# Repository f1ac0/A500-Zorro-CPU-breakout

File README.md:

# A500-Zorro-CPU-breakout
This is a breakout PCB with a DIP64 68000 CPU socket that plugs into the Amiga 500 expansion port. It has no active part and is designed to just move the original 68000 outside the system, host a 68000 CPU replacement, or an expansion designed to seat under the CPU. It should be helpful for design and test purposes, and may use a ZIF-64 socket.

It is designed as a 2 layers board and to fit in the dimensions for cheap PCB manufacturing ; because of this it requires an additional small board for the power pins of the expansion connector (or two additional wires).

Beware that the 68000 is rotated 180° from how it is on the A500 motherboard : its pin 1 is on the top left instead of bottom right. This made the PCB routing a bit more complicated but should allow to install the boards that normally expand over the ROM or Denise chips.

If your CPU replacement does not use bus arbitration to take over the 68k bus, then the CPU on the A500 motherboard must be removed.

Depending on your A500 motherboard revision, you may have to close its JP6 jumper to feed the 7MHz clock to the expansion connector.

# Disclaimer
This is a hobbyist project, it comes with no warranty and no support. Also remember that the Amiga machines are about 30 years old and may fail because of such hardware expansions.

I publish my work under the CC-BY-NC-SA license.

If you find it useful and want to reward my hard work : I am always looking for Amiga/Amstrad CPC/Commodore hardware to repair and hack, please contact me.

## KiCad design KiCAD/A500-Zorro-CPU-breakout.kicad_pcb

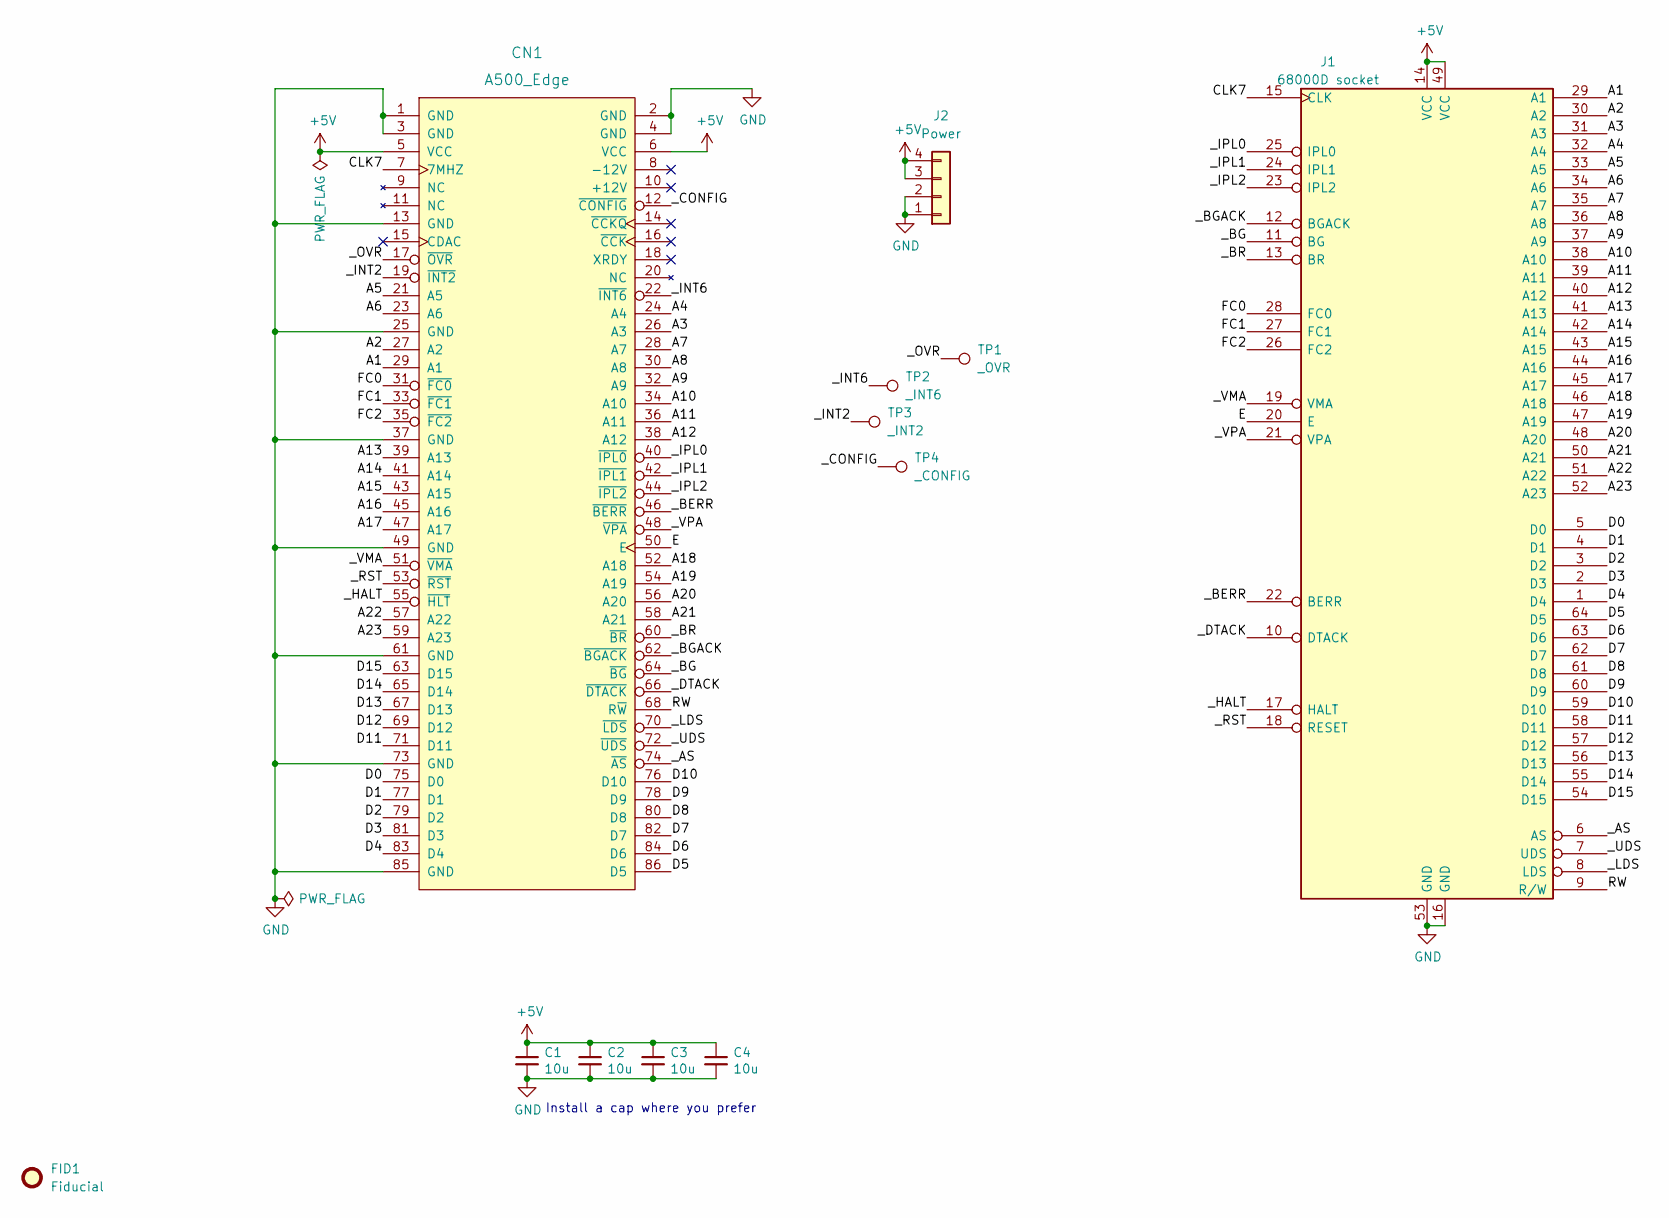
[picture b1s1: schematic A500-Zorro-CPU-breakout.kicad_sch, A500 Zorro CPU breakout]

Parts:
C1, C2, C3, C4: 10u; C_0805_2012Metric
CN1: A500_Edge; A500_ExpansionSocket_2x43_P2.54mm_5mm
FID1: Fiducial; CC_BY_NC_SA_long_silkscreen
J1: 68000D socket; DIP-64_W22.86mm_Socket_LongPads_BigHoles1.0
J2: Power; PinHeader_1x04_P2.54mm_Vertical
TP1: _OVR; TestPoint_THTPad_D1.7mm_Drill1.0mm
TP2: _INT6; TestPoint_THTPad_D1.7mm_Drill1.0mm
TP3: _INT2; TestPoint_THTPad_D1.7mm_Drill1.0mm
TP4: _CONFIG; TestPoint_THTPad_D1.7mm_Drill1.0mm

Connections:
+5V: C1.1, C2.1, C3.1, C4.1, CN1.5 (VCC), CN1.6 (VCC), J1.14 (VCC), J1.49 (VCC), J2.3, J2.4
/A1: CN1.29 (A1), J1.29 (A1)
/A2: CN1.27 (A2), J1.30 (A2)
/A3: CN1.26 (A3), J1.31 (A3)
/A4: CN1.24 (A4), J1.32 (A4)
/A5: CN1.21 (A5), J1.33 (A5)
/A6: CN1.23 (A6), J1.34 (A6)
/A7: CN1.28 (A7), J1.35 (A7)
/A8: CN1.30 (A8), J1.36 (A8)
/A9: CN1.32 (A9), J1.37 (A9)
/A10: CN1.34 (A10), J1.38 (A10)
/A11: CN1.36 (A11), J1.39 (A11)
/A12: CN1.38 (A12), J1.40 (A12)
/A13: CN1.39 (A13), J1.41 (A13)
/A14: CN1.41 (A14), J1.42 (A14)
/A15: CN1.43 (A15), J1.43 (A15)
/A16: CN1.45 (A16), J1.44 (A16)
/A17: CN1.47 (A17), J1.45 (A17)
/A18: CN1.52 (A18), J1.46 (A18)
/A19: CN1.54 (A19), J1.47 (A19)
/A20: CN1.56 (A20), J1.48 (A20)
/A21: CN1.58 (A21), J1.50 (A21)
/A22: CN1.57 (A22), J1.51 (A22)
/A23: CN1.59 (A23), J1.52 (A23)
/CLK7: CN1.7 (7MHZ), J1.15 (CLK)
/D0: CN1.75 (D0), J1.5 (D0)
/D1: CN1.77 (D1), J1.4 (D1)
/D2: CN1.79 (D2), J1.3 (D2)
/D3: CN1.81 (D3), J1.2 (D3)
/D4: CN1.83 (D4), J1.1 (D4)
/D5: CN1.86 (D5), J1.64 (D5)
/D6: CN1.84 (D6), J1.63 (D6)
/D7: CN1.82 (D7), J1.62 (D7)
/D8: CN1.80 (D8), J1.61 (D8)
/D9: CN1.78 (D9), J1.60 (D9)
/D10: CN1.76 (D10), J1.59 (D10)
/D11: CN1.71 (D11), J1.58 (D11)
/D12: CN1.69 (D12), J1.57 (D12)
/D13: CN1.67 (D13), J1.56 (D13)
/D14: CN1.65 (D14), J1.55 (D14)
/D15: CN1.63 (D15), J1.54 (D15)
/E: CN1.50 (E), J1.20 (E)
/FC0: CN1.31 (~FC0), J1.28 (FC0)
/FC1: CN1.33 (~FC1), J1.27 (FC1)
/FC2: CN1.35 (~FC2), J1.26 (FC2)
/RW: CN1.68 (R~W), J1.9 (R/W)
/_AS: CN1.74 (~AS), J1.6 (AS)
/_BERR: CN1.46 (~BERR), J1.22 (BERR)
/_BG: CN1.64 (~BG), J1.11 (BG)
/_BGACK: CN1.62 (~BGACK), J1.12 (BGACK)
/_BR: CN1.60 (~BR), J1.13 (BR)
/_CONFIG: CN1.12 (~CONFIG), TP4.1
/_DTACK: CN1.66 (~DTACK), J1.10 (DTACK)
/_HALT: CN1.55 (~HLT), J1.17 (HALT)
/_INT2: CN1.19 (~INT2), TP3.1
/_INT6: CN1.22 (~INT6), TP2.1
/_IPL0: CN1.40 (~IPL0), J1.25 (IPL0)
/_IPL1: CN1.42 (~IPL1), J1.24 (IPL1)
/_IPL2: CN1.44 (~IPL2), J1.23 (IPL2)
/_LDS: CN1.70 (~LDS), J1.8 (LDS)
/_OVR: CN1.17 (~OVR), TP1.1
/_RST: CN1.53 (~RST), J1.18 (RESET)
/_UDS: CN1.72 (~UDS), J1.7 (UDS)
/_VMA: CN1.51 (~VMA), J1.19 (VMA)
/_VPA: CN1.48 (~VPA), J1.21 (VPA)
GND: C1.2, C2.2, C3.2, C4.2, CN1.1 (GND), CN1.2 (GND), CN1.3 (GND), CN1.4 (GND), CN1.13 (GND), CN1.25 (GND), CN1.37 (GND), CN1.49 (GND), CN1.61 (GND), CN1.73 (GND), CN1.85 (GND), J1.16 (GND), J1.53 (GND), J2.1, J2.2

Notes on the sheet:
Install a cap where you prefer

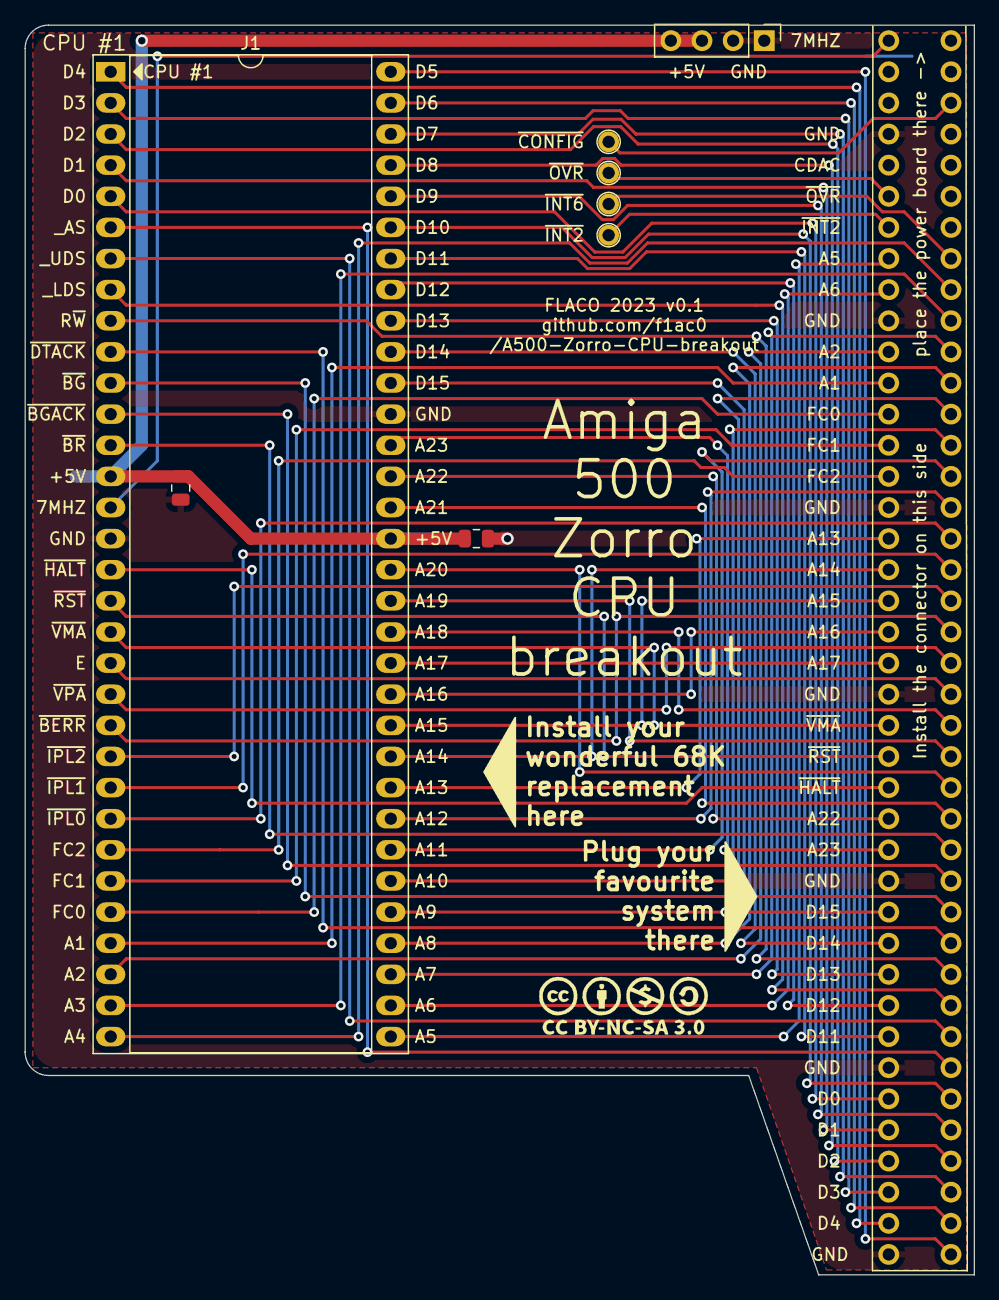
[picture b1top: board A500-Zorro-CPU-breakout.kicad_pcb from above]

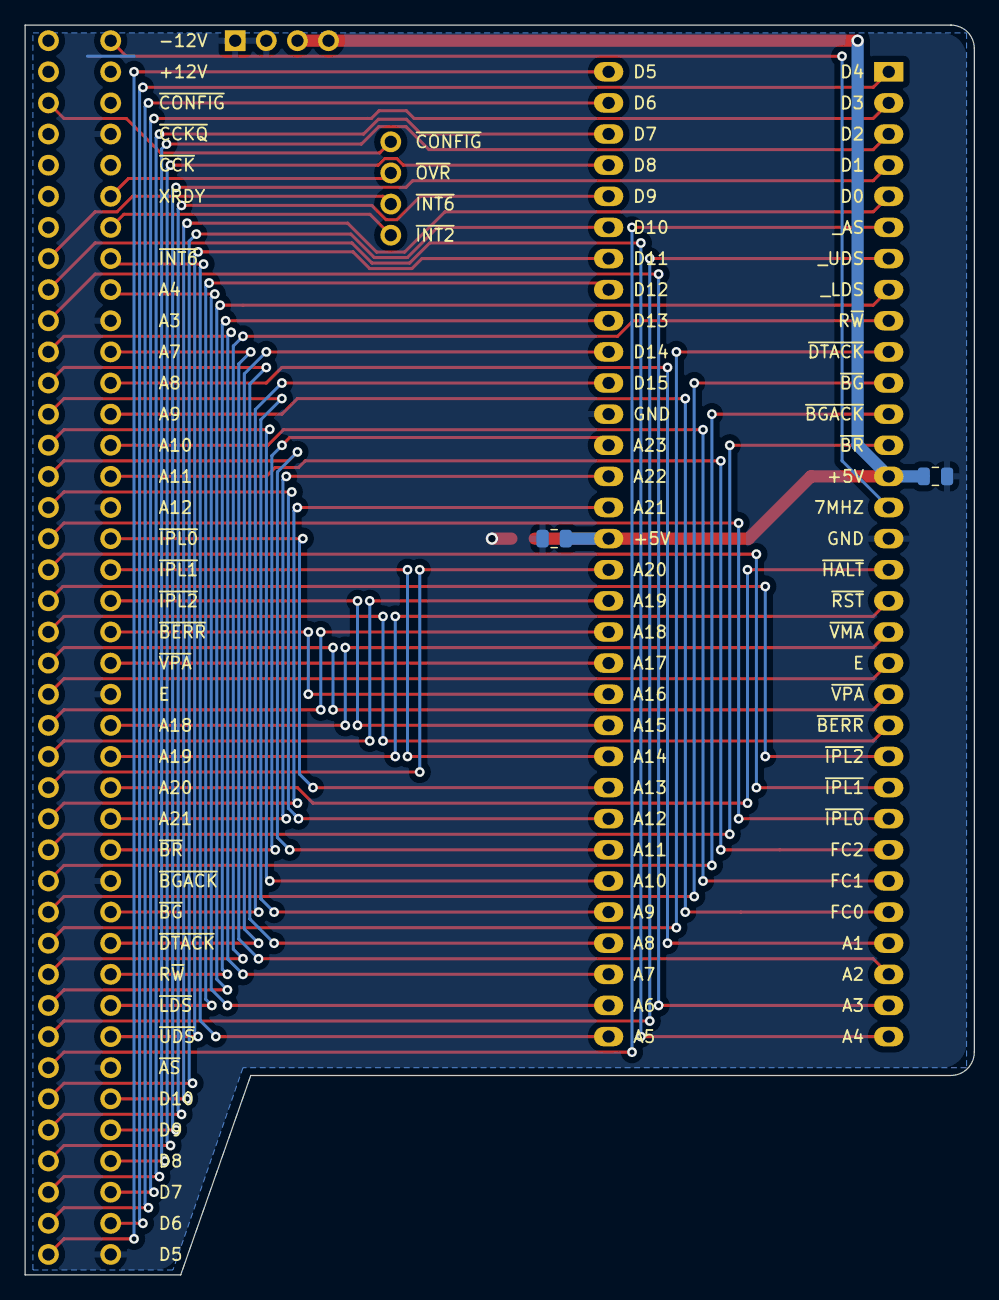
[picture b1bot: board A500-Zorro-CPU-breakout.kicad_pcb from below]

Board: 2 copper layers, 77.5 x 102.0 mm, 12 parts (2 on the bottom side), 66 nets.

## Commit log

2023-06-05 Respository init with KiCAD files, Readme and License

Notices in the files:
KiCAD/A500-Zorro-CPU-breakout.kicad_sch:
FLACO 2023 CC-BY-NC-SA
